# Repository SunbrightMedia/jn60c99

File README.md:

# JUNO-60 (JU-06A) → C99, bit-exact — and onto real hardware

A **bit-exact C99 port** of the Roland Cloud JUNO-60 VST3 DSP engine, proven
against the plugin's own machine code, playable in the browser, and being
carried onto ESP32-S3 hardware as a real instrument. The method is designed to
be REPEATED for the next synth (the JX-3P port is underway in `jx3p/`).

**The one rule:** the original plugin binary (pinned + checksummed in
[`truth/`](truth/)) is the ONLY ground truth. Every constant is proven by
EXECUTING the binary under emulation — no captures, no ear A/B, no fitted
curves. The port is self-proving: `make verify` green = zero non-PROVEN rows
in [`PROVENANCE.tsv`](PROVENANCE.tsv) (status: 20/20 PROVEN).

## Read these, in this order

1. [`END_GOAL.md`](END_GOAL.md) — WHAT we build (user's words, binding)
2. [`CLAUDE.md`](CLAUDE.md) — rules + live state (the constitution)
3. [`FINAL_GUIDE.md`](FINAL_GUIDE.md) — the only status page (tracks A–E)
4. [`docs/INDEX.md`](docs/INDEX.md) — every doc classified, with the question
   it answers
5. [`docs/HISTORY.md`](docs/HISTORY.md) — the full dated log

## The arcs

| Arc | Where | State |
|---|---|---|
| Desktop bit-exact port | `src/` + `tools/verify/` | SEALED — `make verify` green |
| Browser (WASM) | `gui/web/` | Shipped; `wasm_golden` proves WASM == native |
| Engine B (fast fork for hardware) | `engine_b/` | Trunk bit-exact; fork = the sonic-gated S3 engine |
| ONE BOARD per synth (user rule 2026-09-23) | [`END_GOAL.md`](END_GOAL.md) top, [`docs/ONE_BOARD_BUDGET.md`](docs/ONE_BOARD_BUDGET.md) | Every multi-chip plan (two chips, CHAIN4 four boards) is retired history |
| ESP32-S3 firmware | `esp32s3/` | Playable (console, patch step, MIDI UART) |
| Bare-metal Pi (one BCM2837) | `pi/` + [`docs/pi/PORT_PI.md`](docs/pi/PORT_PI.md) | Bit-exact JUNO on metal under QEMU; paused — ask the user |
| Hardware (mix-and-match boards) | [`docs/hardware/`](docs/hardware/) | User draws the boards; BOM v2 + ordering steps ready |
| JX-3P (the repeat) | `jx3p/` | Done: recall + full chain EXACTLY 0, listen proofs, web app |
| JUPITER-8 | `jp8/` | Lifted x86 -> C99, layer gates on the corrected drive; engine + full-chain gate next |
| TB-303 | `tb303/` | Intake + cost recon only |

## Quick start (desktop)

```
make libjuno.so     # build the engine (shared lib for the GUI + gates)
make test           # functional test suite
make verify         # + the LIVE plugin comparisons — the honest finish line
python3 tools/verify/truth.py     # verify ground-truth checksums
bash gui/web/build.sh             # rebuild the WASM app (needs emscripten)
node tools/verify/wasm_golden.mjs # prove WASM == native, bit-exact
```

ESP32-S3: see `esp32s3/LISTEN.md` (build + the canonical flag line) and
`esp32s3/flash/README.md` (prebuilt images, flash commands, no toolchain
needed). Engine-B gates: `tools/engineb/` (`o2_gates.sh`, `o3_gates.sh`, …).

## Layout

| Path | What |
|---|---|
| `truth/` | The plugin + Script.xml + factory bank, checksummed. Paths ONLY via `tools/verify/truth.py` |
| `src/` | The FROZEN bit-exact port (C99). Do not touch except through a gate |
| `tests/` | The unit battery (`make test`) |
| `tools/` | The gates and the Unicorn oracle (`tools/verify/`), the one-command reproduction (`tools/repro/`), the engine B tools and the per-synth configs (`tools/engineb/`, `tools/engineb/synth/`), the parked Track B and its native kernels (`tools/trackb/`) |
| `probes/` | Executed evidence per investigation (each dir has a README) |
| `gui/` | The web app (WASM), the plugin's own skin, the JUNO-60.exe sources, the Tk test GUI |
| `engine_b/` | The fast engine (trunk = bit-exact; fork = S3 flags) and its input boundary (`engine_b/event/`) |
| `esp32s3/` | ESP32-S3 firmware (the live device target) and its images |
| `pi/` | The bare-metal Raspberry Pi build (Circle submodule) |
| `jx3p/`, `jp8/`, `tb303/` | The next synths' ports -- proof the method repeats |
| `refs/` | The decompile archive (provenance for READ claims) and a June live-plugin memory dump (`refs/state_dump/`, diagnostic only) |
| `archive/` | Retired device targets: the Daisy Seed and Teensy builds (history) |
| `docs/` | All findings -- start at `docs/INDEX.md`; the user's older charters `docs/GOAL.md`, `docs/AIRTIGHT_PLAN.md` |
| `bench/` | The job registry (`tools/run_job.sh`, `tools/status.sh`) |
| root files | `CLAUDE.md` (agent rules), `END_GOAL.md` (the goal), `FINAL_GUIDE.md` (the status page), `PROVENANCE.tsv` + `COVERAGE.tsv` (the proof ledgers the gates read), `Makefile`, `juno.dll` (the prebuilt Windows library the GUIs load), `package.json` + `package-lock.json` (the Node packages of the browser checks); `.gitmodules` (the Pi's Circle submodule), `.gitignore`, `.claude/` (the agent's project settings; its `workflows/` are retired -- CLAUDE.md forbids multi-agent workflows) |

Agent rules, hard covenants (captures are forbidden), and the live state all
live in [`CLAUDE.md`](CLAUDE.md).

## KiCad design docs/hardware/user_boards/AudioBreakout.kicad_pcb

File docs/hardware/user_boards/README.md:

# user_boards — snapshots of the user's own KiCad files (REFERENCE, saved 2026-09-28)

The user draws every schematic and PCB by hand; the CURRENT files live on the user's PC. These are the latest copies the
user uploaded to the retired chat (upload date in brackets), kept so a new session can audit nets without asking again.
Never treat them as newer than what the user has; ask for a fresh upload before any audit that matters.

| file | what | uploaded |
|---|---|---|
| EspMotherboard.kicad_sch | ESP32-S3 motherboard (N16R8 DevKitC-1 socket, headers to every satellite board) | 2026-09-21 |
| HeadphoneBreakout.kicad_sch | headphone / DAC board (= Headphone_Dac in the BOM) | 2026-09-21 |
| AudioBreakout.kicad_sch + .kicad_pcb | the audio breakout (PCM5102A DAC, OPA1656 line drivers, TPA6120 HP amp, LM2776 -5 V) | 2026-09-21 |
| buttonpack3.kicad_sch | 3-button pack (PB86-A1 3-Pack) | 2026-09-22 |
| muxboardv1.kicad_sch | CD74HC4067 16-channel mux board (Multiplex16) | 2026-09-21 |
| EVERY_PCB_FILES_2026-09-23.zip | the user's JLC export of all 14 boards (gerbers + bom + designators + netlist per board); the BOM inputs in `../bom/inputs/` come from it | 2026-09-23 |

The SegmentBackpack schematic is in `../SegmentBackpack/`, the Switch/Fader boards in `../SwitchBoard/` and `../FaderBoard/`.
Audit any of them with `tools/hardware/schem_audit.py FILE --tooth` first (docs/hardware/AUDIT.md).

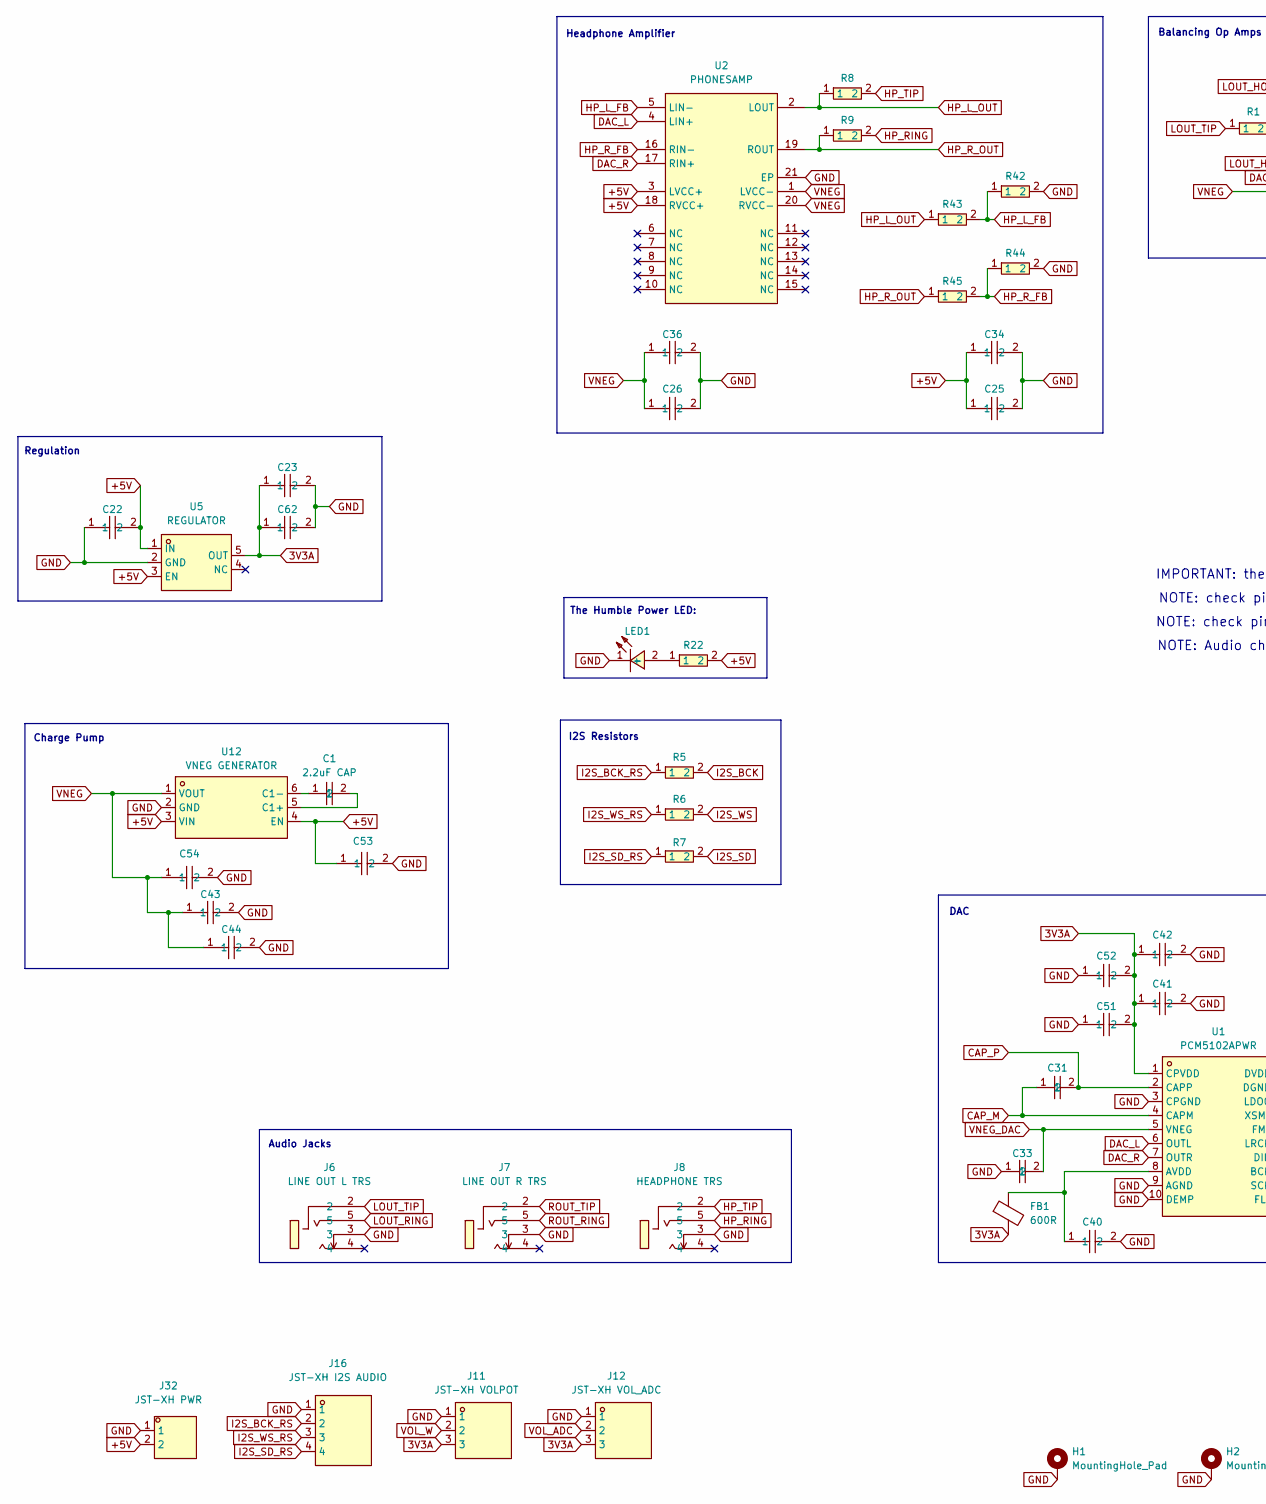
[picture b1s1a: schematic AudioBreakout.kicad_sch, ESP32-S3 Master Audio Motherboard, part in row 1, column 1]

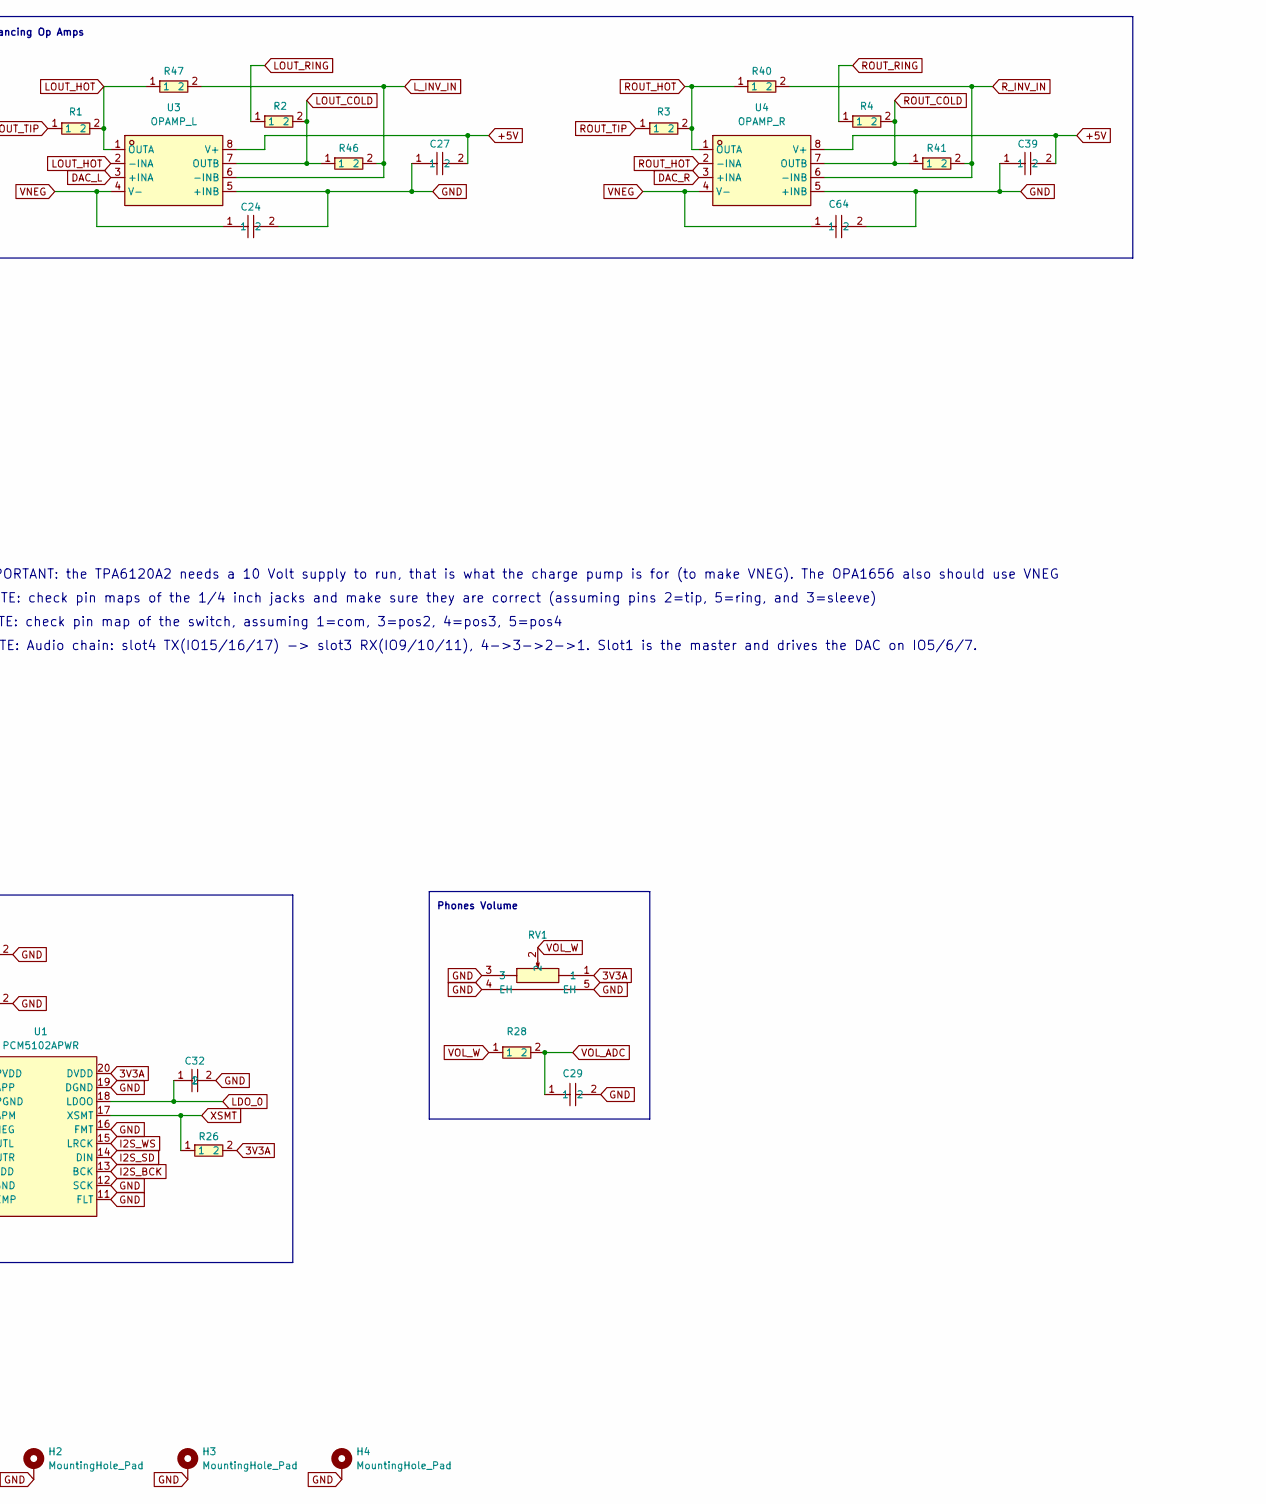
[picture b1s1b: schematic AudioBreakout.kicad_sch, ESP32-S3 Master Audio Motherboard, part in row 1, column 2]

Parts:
C1: 2.2uF CAP; C0603; MPN CL10A225KO8NNNC; LCSC Part C23630
C22, C23, C51, C52, C53, C54: CL21A106KAYNNNE; C0805; MPN CL21A106KAYNNNE; LCSC Part C15850
C24, C27, C29, C34, C36, C39, C40, C41, C42, C62, C64: CC0603KRX7R9BB104; C0603; MPN CC0603KRX7R9BB104; LCSC Part C14663
C25, C26, C43, C44: CL21A226MAQNNNE; C0805; MPN CL21A226MAQNNNE; LCSC Part C45783
C31, C32, C33: CL10A225KO8NNNC; C0603; MPN CL10A225KO8NNNC; LCSC Part C23630
FB1: 600R; R_0805_2012Metric; LCSC Part C46550600
H1, H2, H3, H4: MountingHole_Pad; MountingHole_3.2mm_M3_Pad
J6: LINE OUT L TRS; AUDIO-TH_PJ-603; MPN PJ-603; LCSC Part C41409498
J7: LINE OUT R TRS; AUDIO-TH_PJ-603; MPN PJ-603; LCSC Part C41409498
J8: HEADPHONE TRS; AUDIO-TH_PJ-603; MPN PJ-603; LCSC Part C41409498
J11: JST-XH VOLPOT; CONN-TH_S3B-XH-A-LF-SN; MPN S3B-XH-A(LF)(SN); LCSC Part C157928
J12: JST-XH VOL_ADC; CONN-TH_S3B-XH-A-LF-SN; MPN S3B-XH-A(LF)(SN); LCSC Part C157928
J16: JST-XH I2S AUDIO; CONN-TH_S4B-XH-A-LF-SN; MPN S4B-XH-A(LF)(SN); LCSC Part C157925
J32: JST-XH PWR; CONN-TH_S2B-XH-A-LF-SN; MPN S2B-XH-A(LF)(SN); LCSC Part C157931
LED1: FC-2012YOXK; LED0805-RD_ORANGE; MPN NCD0805O1; LCSC Part C84262
R1, R2, R3, R4, R5, R6, R7: 0603WAF330JT5E; R0603; MPN 0603WAF330JT5E; LCSC Part C23140
R8, R9: 0603WAF100JT5E; R0603; MPN 0603WAF100JT5E; LCSC Part C22859
R22, R26, R28: 0805W8F1002T5E; R0805; MPN 0805W8F1002T5E; LCSC Part C17414
R40, R41, R42, R43, R44, R45, R46, R47: 0603WAF1001T5E; R0603; MPN 0603WAF1001T5E; LCSC Part C21190
RV1: RK09K1130A70; RES-TH_RK09K1130A70; MPN RK09K1130A70; LCSC Part C351173
U1: PCM5102APWR; TSSOP-20_L6.5-W4.4-P0.65-LS6.4-BL; MPN PCM5102APWR; LCSC Part C107671
U2: PHONESAMP; HSOP-20_L12.9-W7.5-P1.27-BL-EP; MPN TPA6120A2DWPR; LCSC Part C70439
U3: OPAMP_L; SOIC-8_L4.9-W3.9-P1.27-LS6.0-BL; MPN OPA1656IDR; LCSC Part C1849431
U4: OPAMP_R; SOIC-8_L4.9-W3.9-P1.27-LS6.0-BL; MPN OPA1656IDR; LCSC Part C1849431
U5: REGULATOR; SOT-23-5_L2.9-W1.6-P0.95-LS2.8-BR; MPN TPS7A2033PDBVR; LCSC Part C2862740
U12: VNEG GENERATOR; SOT-23-6_L2.9-W1.6-P0.95-LS2.8-BR; MPN LM2776DBVR; LCSC Part C69527

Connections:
3V3A: C23.1, C41.1, C42.1, C51.2, C52.2, C62.1, FB1.2, J11.3, J12.3, R26.2, RV1.1, U1.1 (CPVDD), U1.20 (DVDD), U5.5 (OUT)
+5V: C22.2, C25.1, C27.2, C34.1, C39.2, C53.1, J32.2, R22.2, U2.3 (LVCC+), U2.18 (RVCC+), U3.8 (V+), U4.8 (V+), U5.1 (IN), U5.3 (EN), U12.3 (VIN), U12.4 (EN)
CAP_M: C31.1, U1.4 (CAPM)
CAP_P: C31.2, U1.2 (CAPP)
DAC_L: U1.6 (OUTL), U2.4 (LIN+), U3.3 (+INA)
DAC_R: U1.7 (OUTR), U2.17 (RIN+), U4.3 (+INA)
GND: C22.1, C23.2, C24.2, C25.2, C26.2, C27.1, C29.2, C32.2, C33.1, C34.2, C36.2, C39.1, C40.2, C41.2, C42.2, C43.2, C44.2, C51.1, C52.1, C53.2, C54.2, C62.2, C64.2, H1.1 (1_1), H2.1 (1_1), H3.1 (1_1), H4.1 (1_1), J6.3, J7.3, J8.3, J11.1, J12.1, J16.1, J32.1, LED1.1 (-), R42.2, R44.2, RV1.3, RV1.4 (EH), RV1.5 (EH), U1.3 (CPGND), U1.9 (AGND), U1.10 (DEMP), U1.11 (FLT), U1.12 (SCK), U1.16 (FMT), U1.19 (DGND), U2.21 (EP), U3.5 (+INB), U4.5 (+INB), U5.2 (GND), U12.2 (GND)
HP_L_FB: R42.1, R43.2, U2.5 (LIN-)
HP_L_OUT: R8.1, R43.1, U2.2 (LOUT)
HP_RING: J8.5, R9.2
HP_R_FB: R44.1, R45.2, U2.16 (RIN-)
HP_R_OUT: R9.1, R45.1, U2.19 (ROUT)
HP_TIP: J8.2, R8.2
I2S_BCK: R5.2, U1.13 (BCK)
I2S_BCK_RS: J16.2, R5.1
I2S_SD: R7.2, U1.14 (DIN)
I2S_SD_RS: J16.4, R7.1
I2S_WS: R6.2, U1.15 (LRCK)
I2S_WS_RS: J16.3, R6.1
LDO_0: C32.1, U1.18 (LDOO)
LOUT_COLD: R2.2, R46.1, U3.7 (OUTB)
LOUT_HOT: R1.2, R47.1, U3.1 (OUTA), U3.2 (-INA)
LOUT_RING: J6.5, R2.1
LOUT_TIP: J6.2, R1.1
L_INV_IN: R46.2, R47.2, U3.6 (-INB)
unnamed: LED1.2 (+), R22.1
unnamed: C40.1, FB1.1, U1.8 (AVDD)
unnamed: C1.2, U12.5 (C1+)
unnamed: C1.1, U12.6 (C1-)
ROUT_COLD: R4.2, R41.1, U4.7 (OUTB)
ROUT_HOT: R3.2, R40.1, U4.1 (OUTA), U4.2 (-INA)
ROUT_RING: J7.5, R4.1
ROUT_TIP: J7.2, R3.1
R_INV_IN: R40.2, R41.2, U4.6 (-INB)
VNEG: C24.1, C26.1, C36.1, C43.1, C44.1, C54.1, C64.1, U2.1 (LVCC-), U2.20 (RVCC-), U3.4 (V-), U4.4 (V-), U12.1 (VOUT)
VNEG_DAC: C33.2, U1.5 (VNEG)
VOL_ADC: C29.1, J12.2, R28.2
VOL_W: J11.2, R28.1, RV1.2
XSMT: R26.1, U1.17 (XSMT)

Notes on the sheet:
Headphone Amplifier
Charge Pump
I2S Resistors
NOTE: check pin maps of the 1/4 inch jacks and make sure they are correct (assuming pins 2=tip, 5=ring, and 3=sleeve)
Regulation
Audio Jacks
NOTE: check pin map of the switch, assuming 1=com, 3=pos2, 4=pos3, 5=pos4
IMPORTANT: the TPA6120A2 needs a 10 Volt supply to run, that is what the charge pump is for (to make VNEG). The OPA1656 also should use VNEG
The Humble Power LED:
Phones Volume
NOTE: Audio chain: slot4 TX(IO15/16/17) -> slot3 RX(IO9/10/11), 4->3->2->1. Slot1 is the master and drives the DAC on IO5/6/7.
DAC
Balancing Op Amps

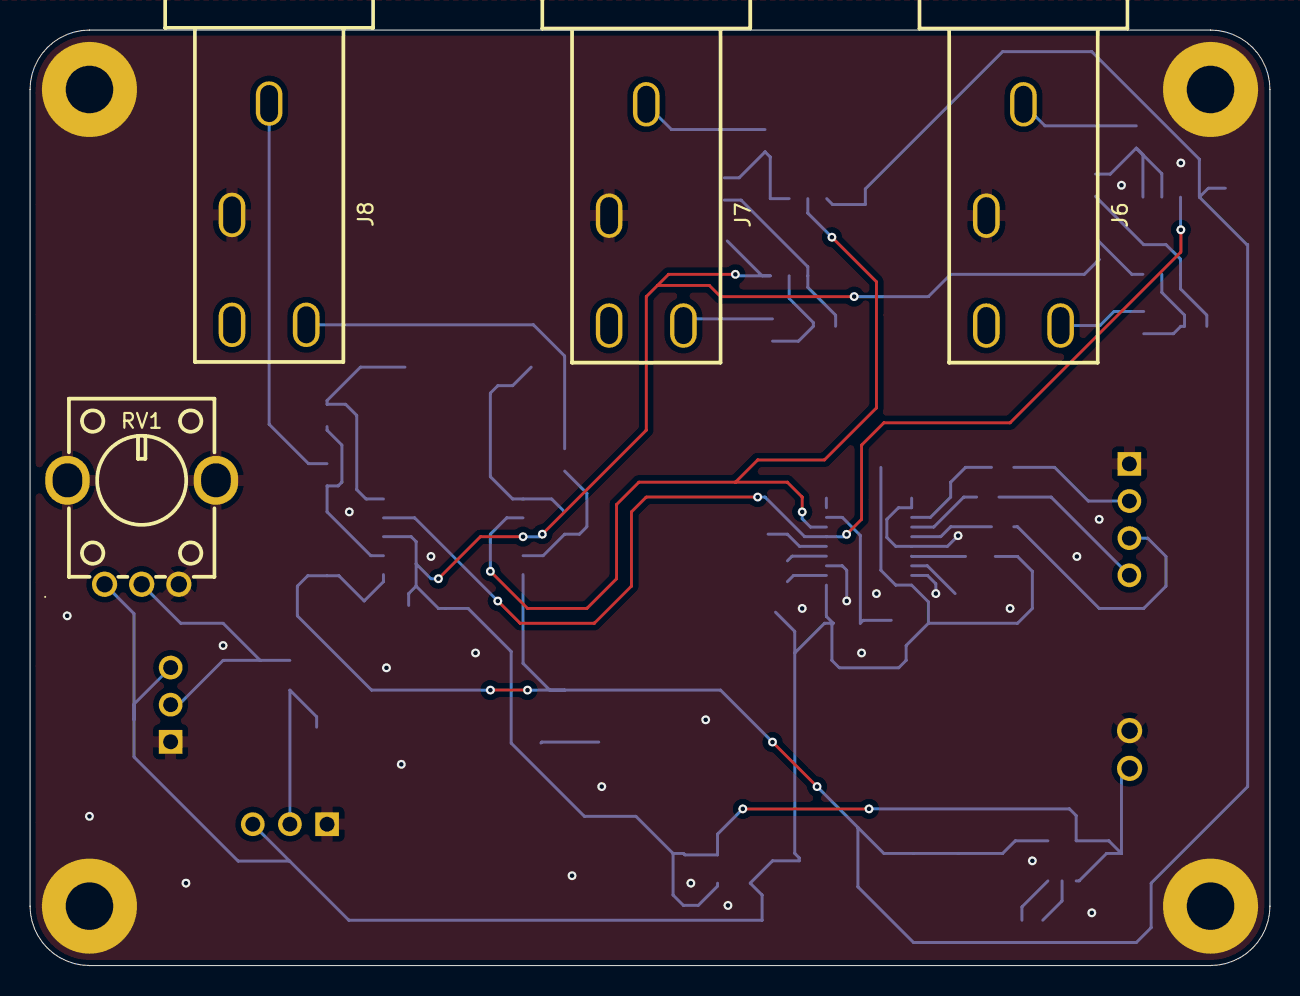
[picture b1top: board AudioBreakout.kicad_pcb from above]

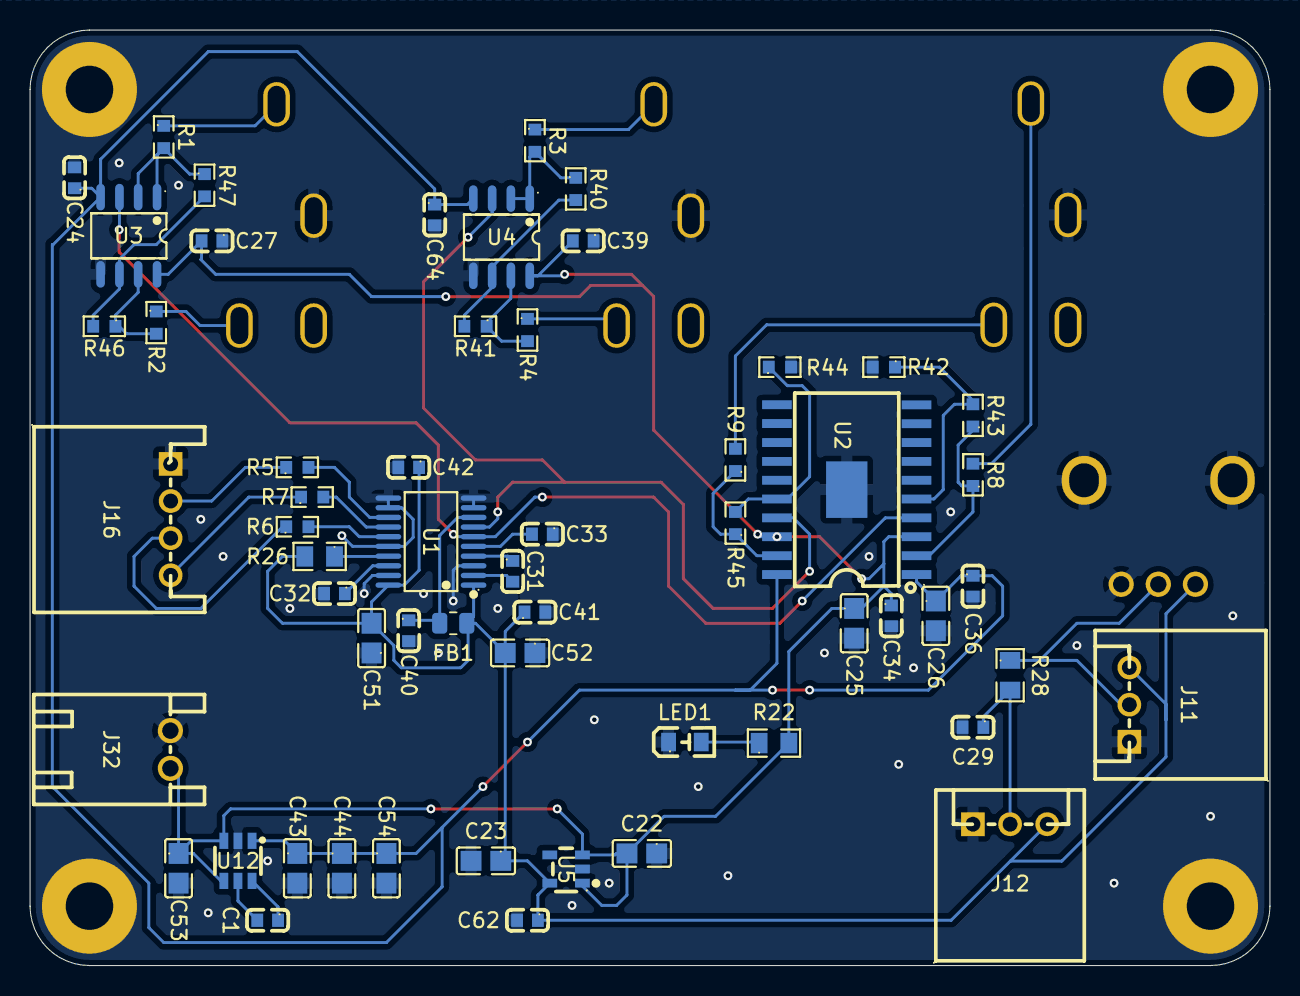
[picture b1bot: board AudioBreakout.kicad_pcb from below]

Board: 4 copper layers, 83.5 x 63.0 mm, 65 parts (57 on the bottom side), 39 nets.

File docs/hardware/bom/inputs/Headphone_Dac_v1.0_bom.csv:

Designator,Footprint,Quantity,Value,LCSC Part #
C1,C0603,1,2.2uF CAP,C23630
"C25, C26, C43, C44",C0805,4,CL21A226MAQNNNE,C45783
"C31, C32, C33",C0603,3,CL10A225KO8NNNC,C23630
"C34, C36, C40, C41, C42",C0603,5,CC0603KRX7R9BB104,C14663
"C51, C52, C53, C54",C0805,4,CL21A106KAYNNNE,C15850
FB1,0805,1,600R,C46550600
LED1,LED0805-RD_ORANGE,1,FC-2012YOXK,C84262
"R22, R26",R0805,2,0805W8F1002T5E,C17414
"R42, R43, R44, R45",R0603,4,0603WAF1001T5E,C21190
"R5, R6, R7",R0603,3,0603WAF330JT5E,C23140
"R8, R9",R0603,2,0603WAF100JT5E,C22859
U1,TSSOP-20_L6.5-W4.4-P0.65-LS6.4-BL,1,PCM5102APWR,C107671
U12,SOT-23-6_L2.9-W1.6-P0.95-LS2.8-BR,1,VNEG GENERATOR,C69527
U2,HSOP-20_L12.9-W7.5-P1.27-BL-EP,1,PHONESAMP,C70439

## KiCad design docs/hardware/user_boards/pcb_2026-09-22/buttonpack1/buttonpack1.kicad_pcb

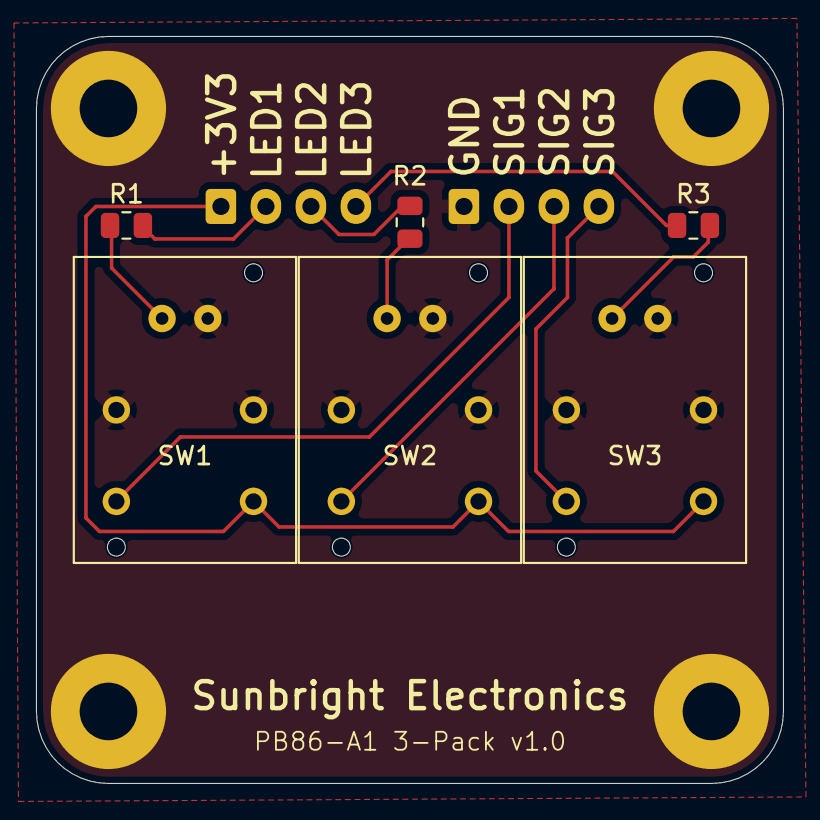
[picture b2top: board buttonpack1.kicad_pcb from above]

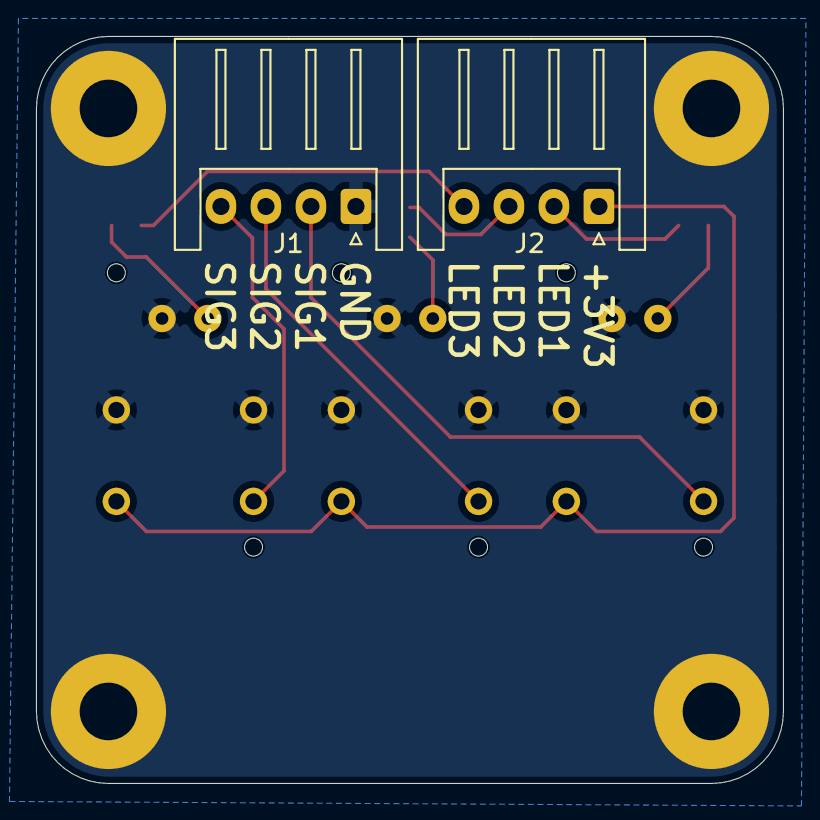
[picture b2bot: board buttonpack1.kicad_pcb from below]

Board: 2 copper layers, 41.5 x 41.5 mm, 12 parts (2 on the bottom side), 11 nets.

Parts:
H1, H2, H3, H4: HOLE_M3; MountingHole_3.2mm_M3_Pad
J1: CN_Button; JST_XH_S4B-XH-A_1x04_P2.50mm_Horizontal
J2: CN_LED; JST_XH_S4B-XH-A_1x04_P2.50mm_Horizontal
R1, R2, R3: 220; R_0805_2012Metric
SW1: PB86_1; PB_86_A1
SW2: PB86_2; PB_86_A1
SW3: PB86_3; PB_86_A1

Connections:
GND: H1.1 (PAD), H2.1 (PAD), H3.1 (PAD), H4.1 (PAD), J1.1, SW1.1 (B), SW1.6 (LED-), SW2.1 (B), SW2.6 (LED-), SW3.1 (B), SW3.6 (LED-)
LED1: J2.2, R1.1
LED2: J2.3, R2.1
LED3: J2.4, R3.1
unnamed: R1.2, SW1.5 (LED+)
unnamed: R2.2, SW2.5 (LED+)
unnamed: R3.2, SW3.5 (LED+)
SIG1: J1.2, SW1.2 (C)
SIG2: J1.3, SW2.2 (C)
SIG3: J1.4, SW3.2 (C)
VCC: J2.1, SW1.3 (A), SW2.3 (A), SW3.3 (A)

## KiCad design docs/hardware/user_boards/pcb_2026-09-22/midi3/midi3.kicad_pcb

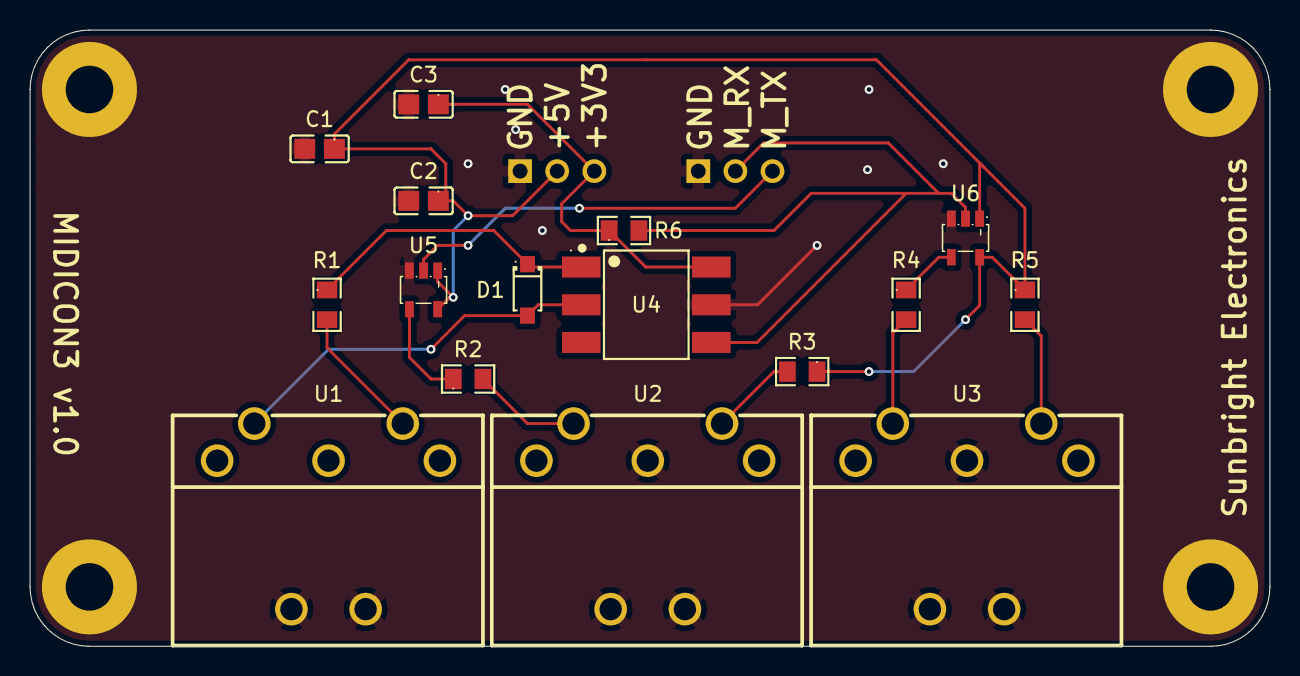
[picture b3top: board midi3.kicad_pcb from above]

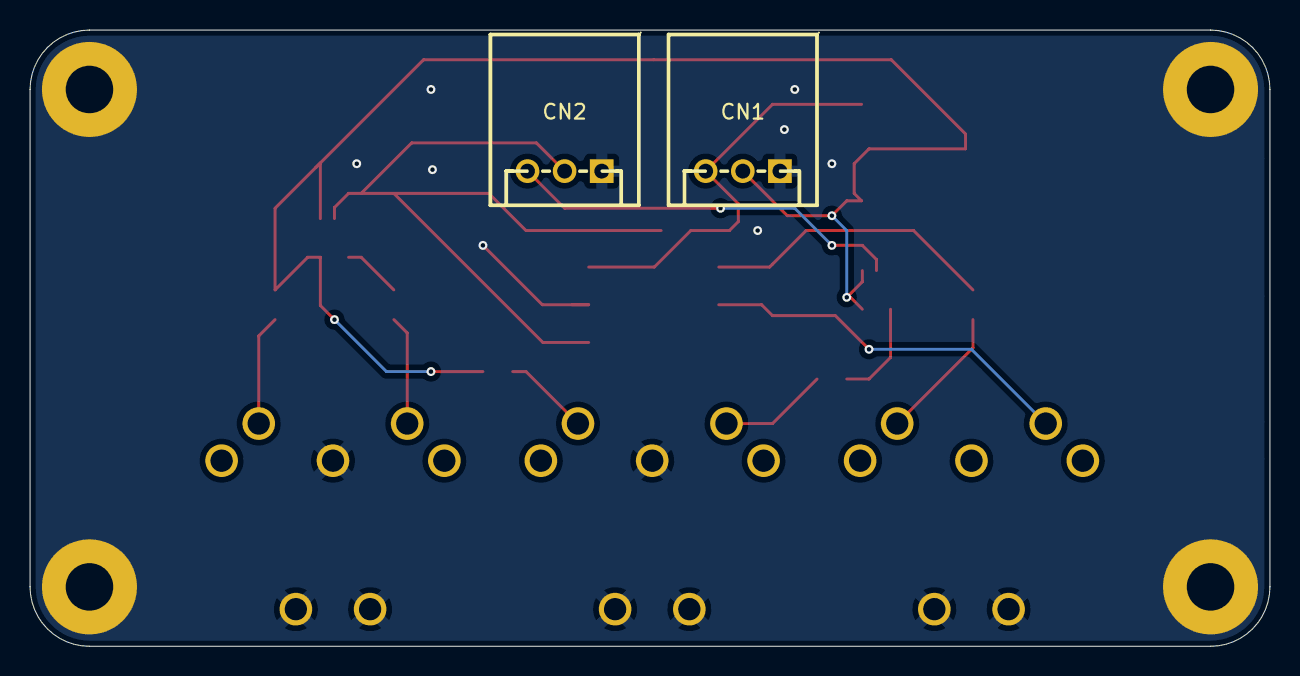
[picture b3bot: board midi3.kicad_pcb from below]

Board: 2 copper layers, 83.5 x 41.5 mm, 22 parts (2 on the bottom side), 14 nets.

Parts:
C1, C2, C3: CC0805KRX7R9BB104; C0805
CN1: CON_PWR; CONN-TH_S3B-XH-A-LF-SN
CN2: CON_SIG; CONN-TH_S3B-XH-A-LF-SN
D1: 1N4148W_C81598; SOD-123F_L2.7-W1.6-LS3.8-RD
H1, H2, H3, H4: MountingHole_Pad; MountingHole_3.2mm_M3_Pad
R1, R2, R3, R4, R5: 0805W8F2200T5E; R0805
R6: 0805W8F1001T5E; R0805
U1: MIDI-IN; CONN-TH_DIN-504D-M5
U2: MIDI-OUT; CONN-TH_DIN-504D-M5
U3: MIDI-THRU; CONN-TH_DIN-504D-M5
U4: OPTOCOUPLER; SMD-6_L7.3-W6.5-P2.54-LS10.2-BL
U5: MIDI-OUT BUFFER; SOT-23-5_L3.0-W1.7-P0.95-LS2.8-BR
U6: MIDI-THRU BUFFER; SOT-23-5_L3.0-W1.7-P0.95-LS2.8-BR

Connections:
+3V3: C3.1, CN1.3, R6.1, U4.6 (VCC)
+5V: C1.1, C2.1, CN1.2, R3.1, R5.1, U5.1 (OE), U5.5 (VCC), U6.1 (OE), U6.5 (VCC)
GND: C1.2, C2.2, C3.2, CN1.1, CN2.1, H1.1, H2.1, H3.1, H4.1, U1.6, U1.7, U2.2, U2.6, U2.7, U3.2, U3.6, U3.7, U4.5 (GND), U5.3 (GND), U6.3 (GND)
MIDI_RX: CN2.2, R6.2, U4.4 (VO), U6.2 (A)
MIDI_TX: CN2.3, U5.2 (A)
unnamed: D1.2 (A), U1.5, U4.2 (CAT)
unnamed: D1.1 (K), R1.1, U4.1 (AN)
unnamed: R1.2, U1.4
unnamed: R2.2, U2.5
unnamed: R3.2, U2.4
unnamed: R4.2, U3.5
unnamed: R5.2, U3.4
unnamed: R2.1, U5.4 (Y)
unnamed: R4.1, U6.4 (Y)

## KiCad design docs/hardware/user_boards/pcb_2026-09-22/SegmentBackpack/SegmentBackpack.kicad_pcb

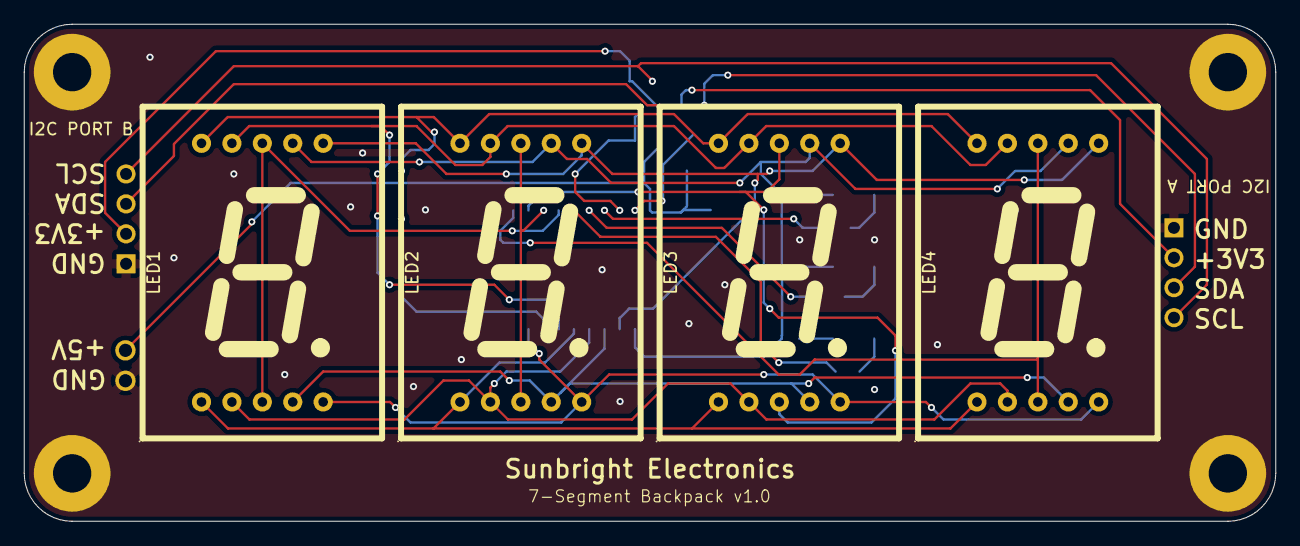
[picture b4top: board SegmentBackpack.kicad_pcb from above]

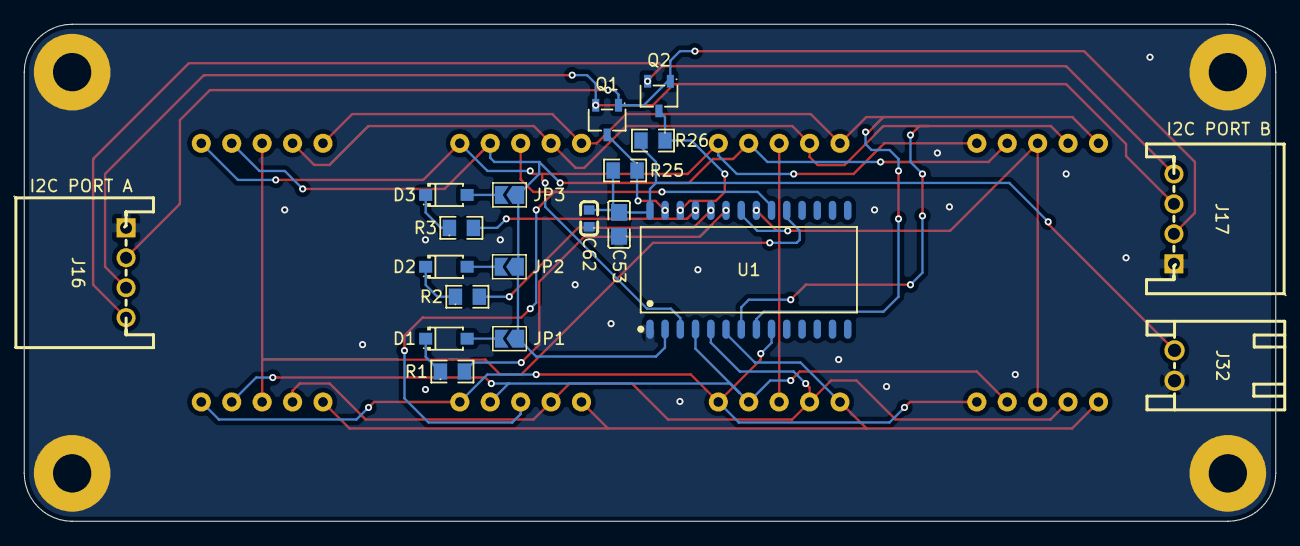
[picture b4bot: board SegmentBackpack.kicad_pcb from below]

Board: 2 copper layers, 104.5 x 41.5 mm, 27 parts (19 on the bottom side), 28 nets.

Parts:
C53: CL21A106KAYNNNE; C0805
C62: CC0603KRX7R9BB104; C0603
D1, D2, D3: 1N4148W_C81598; SOD-123F_L2.7-W1.6-LS3.8-RD
H1, H2, H3, H4: HOLE_M3; MountingHole_3.2mm_M3_Pad
J16: I2C IN; CONN-TH_S4B-XH-A-LF-SN
J17: I2C THRU; CONN-TH_S4B-XH-A-LF-SN
J32: PWR; CONN-TH_S2B-XH-A-LF-SN
JP1, JP2, JP3: SolderJumper_2_Open; SolderJumper-2_P1.3mm_Open_TrianglePad1.0x1.5mm
LED1, LED2, LED3, LED4: FJ8106BH; LED-SEG-TH_FJ8106AH
Q1, Q2: BSS138_C52895; SOT-23-3_L2.9-W1.6-P1.90-LS2.8-BR
R1, R2, R3: 0805W8F3902T5E; R0805
R25, R26: 0805W8F1002T5E; R0805
U1: HT16K33A-28SOP; SOP-28_L17.9-W7.5-P1.27-LS10.3-BL

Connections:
+3V3: J16.2, J17.2, Q1.1 (G), Q2.1 (G)
+5V: C53.2, C62.2, J32.2, R25.2, R26.2, U1.28 (VDD)
A0: R1.2, U1.23 (ROW2/A0)
A0_D: D1.1 (K), R1.1
A0_J: D1.2 (A), JP1.2 (B)
A1: R2.2, U1.24 (ROW1/A1)
A1_D: D2.1 (K), R2.1
A1_J: D2.2 (A), JP2.2 (B)
A2: R3.2, U1.25 (ROW0/A2)
A2_D: D3.1 (K), R3.1
A2_J: D3.2 (A), JP3.2 (B)
DIG1: LED1.3 (V1), LED1.8 (V2), U1.22 (ROW3/K1)
DIG2: LED2.3 (V1), LED2.8 (V2), U1.21 (ROW4/K2)
DIG3: LED3.3 (V1), LED3.8 (V2), U1.20 (ROW5/K3)
DIG4: LED4.3 (V1), LED4.8 (V2), U1.19 (ROW6/K4)
GND: C53.1, C62.1, H1.1 (PAD), H2.1 (PAD), H3.1 (PAD), H4.1 (PAD), J16.1, J17.1, J32.1, U1.1 (VSS)
SCL: J16.4, J17.4, Q2.2 (S)
SCL5: Q2.3 (D), R26.1, U1.26 (SCL)
SDA: J16.3, J17.3, Q1.2 (S)
SDA5: Q1.3 (D), R25.1, U1.27 (SDA)
SEG_A: JP1.1 (A), JP2.1 (A), JP3.1 (A), LED1.7 (A), LED2.7 (A), LED3.7 (A), LED4.7 (A), U1.2 (COM0/AD)
SEG_B: LED1.6 (B), LED2.6 (B), LED3.6 (B), LED4.6 (B), U1.3 (COM1/KS0)
SEG_C: LED1.4 (C), LED2.4 (C), LED3.4 (C), LED4.4 (C), U1.4 (COM2/KS1)
SEG_D: LED1.2 (D), LED2.2 (D), LED3.2 (D), LED4.2 (D), U1.5 (COM3/KS2)
SEG_DP: LED1.5 (DP), LED2.5 (DP), LED3.5 (DP), LED4.5 (DP), U1.9 (COM7)
SEG_E: LED1.1 (E), LED2.1 (E), LED3.1 (E), LED4.1 (E), U1.6 (COM4)
SEG_F: LED1.9 (F), LED2.9 (F), LED3.9 (F), LED4.9 (F), U1.7 (COM5)
SEG_G: LED1.10 (G), LED2.10 (G), LED3.10 (G), LED4.10 (G), U1.8 (COM6)

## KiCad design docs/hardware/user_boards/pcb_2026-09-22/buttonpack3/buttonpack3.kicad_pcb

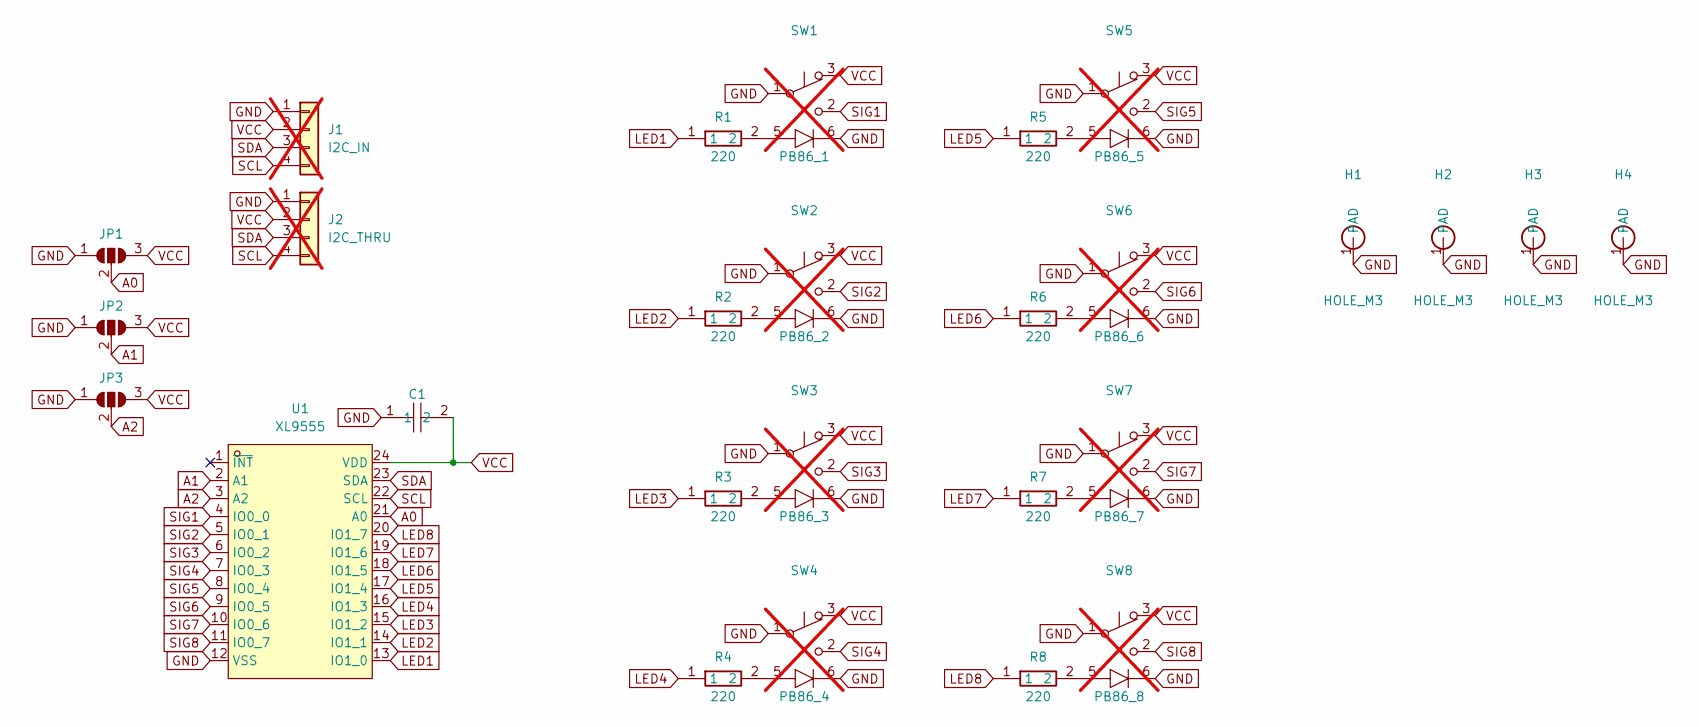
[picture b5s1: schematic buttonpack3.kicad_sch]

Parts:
C1: CC0805KRX7R9BB104; C0805; MPN CC0805KRX7R9BB104; LCSC Part C49678
H1, H2, H3, H4: HOLE_M3; MountingHole_3.2mm_M3_Pad
J1: I2C_IN; JST_XH_S4B-XH-A_1x04_P2.50mm_Horizontal; not fitted
J2: I2C_THRU; JST_XH_S4B-XH-A_1x04_P2.50mm_Horizontal; not fitted
JP1, JP2, JP3: SolderJumper_3_Open; SolderJumper-3_P2.0mm_Open_TrianglePad1.0x1.5mm
R1, R2, R3, R4, R5, R6, R7, R8: 220; R_0805_2012Metric; LCSC Part C17557
SW1: PB86_1; PB_86_A1; not fitted
SW2: PB86_2; PB_86_A1; not fitted
SW3: PB86_3; PB_86_A1; not fitted
SW4: PB86_4; PB_86_A1; not fitted
SW5: PB86_5; PB_86_A1; not fitted
SW6: PB86_6; PB_86_A1; not fitted
SW7: PB86_7; PB_86_A1; not fitted
SW8: PB86_8; PB_86_A1; not fitted
U1: XL9555; TSSOP-24_L7.8-W4.4-P0.65-LS6.4-BL; MPN XL9555; LCSC Part C609791

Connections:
A0: JP1.2 (C), U1.21 (A0)
A1: JP2.2 (C), U1.2 (A1)
A2: JP3.2 (C), U1.3 (A2)
GND: C1.1, H1.1 (PAD), H2.1 (PAD), H3.1 (PAD), H4.1 (PAD), J1.1, J2.1, JP1.1 (A), JP2.1 (A), JP3.1 (A), SW1.1 (B), SW1.6 (LED-), SW2.1 (B), SW2.6 (LED-), SW3.1 (B), SW3.6 (LED-), SW4.1 (B), SW4.6 (LED-), SW5.1 (B), SW5.6 (LED-), SW6.1 (B), SW6.6 (LED-), SW7.1 (B), SW7.6 (LED-), SW8.1 (B), SW8.6 (LED-), U1.12 (VSS); also elsewhere on the board
LED1: R1.1, U1.13 (IO1_0)
LED2: R2.1, U1.14 (IO1_1)
LED3: R3.1, U1.15 (IO1_2)
LED4: R4.1, U1.16 (IO1_3)
LED5: R5.1, U1.17 (IO1_4)
LED6: R6.1, U1.18 (IO1_5)
LED7: R7.1, U1.19 (IO1_6)
LED8: R8.1, U1.20 (IO1_7)
unnamed: R1.2, SW1.5 (LED+)
unnamed: R2.2, SW2.5 (LED+)
unnamed: R3.2, SW3.5 (LED+)
unnamed: R4.2, SW4.5 (LED+)
unnamed: R5.2, SW5.5 (LED+)
unnamed: R6.2, SW6.5 (LED+)
unnamed: R7.2, SW7.5 (LED+)
unnamed: R8.2, SW8.5 (LED+)
SCL: J1.4, J2.4, U1.22 (SCL); also elsewhere on the board
SDA: J1.3, J2.3, U1.23 (SDA); also elsewhere on the board
SIG1: SW1.2 (C), U1.4 (IO0_0)
SIG2: SW2.2 (C), U1.5 (IO0_1)
SIG3: SW3.2 (C), U1.6 (IO0_2)
SIG4: SW4.2 (C), U1.7 (IO0_3)
SIG5: SW5.2 (C), U1.8 (IO0_4)
SIG6: SW6.2 (C), U1.9 (IO0_5)
SIG7: SW7.2 (C), U1.10 (IO0_6)
SIG8: SW8.2 (C), U1.11 (IO0_7)
VCC: C1.2, J1.2, J2.2, JP1.3 (B), JP2.3 (B), JP3.3 (B), SW1.3 (A), SW2.3 (A), SW3.3 (A), SW4.3 (A), SW5.3 (A), SW6.3 (A), SW7.3 (A), SW8.3 (A), U1.24 (VDD); also elsewhere on the board
